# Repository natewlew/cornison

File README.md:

# Cornison

A split mechanical keyboard based on [foostan](https://github.com/foostan)'s
[Corne Cherry v3](https://github.com/foostan/crkbd/tree/v3-final), with a few extra keys
added in a [Keebio Levinson](https://github.com/Keebio/Levinson)-style
layout (an ortholinear grid-plus-thumb-keys arrangement in the same family
as [Let's Split](https://github.com/qmk/qmk_firmware/tree/master/keyboards/lets_split)) —
the name is a mix of **Corne** and **Levinson**.

- **Left half:** the standard Corne 3×6 grid, plus 3 thumb keys and
  dedicated Ctrl, Alt, and Cmd keys.
- **Right half:** the standard Corne 3×6 grid, plus 2 thumb keys and 4
  arrow keys.
- 48 keys total, Kailh/Gateron hotswap sockets (no soldering switches),
  Pro Micro (or Elite-C/Sea-Picro EXT) controller per half, OLED display,
  TRRS between halves, optional per-key and underglow RGB LEDs.
- A 3D-printed case and switch plate, generated directly from the PCB
  rather than hand-modeled, so it stays in sync with any board change.

## Status

**v1.1 is built and in daily use.** Confirmed on real hardware:

- Every key on both halves, the split link over TRRS, and the OLEDs.
- The printed case, FR4 switch plate, inset MCU cover and tenting legs,
  all from the files in this repo.
- A printed PETG switch plate and the spacer frame.
- Pro Micro (Caterina bootloader) as the controller.

Not tested yet:

- Per-key and underglow RGB LEDs.
- Elite-C and Sea-Picro EXT, which should be pin-compatible.
- POM and MJF nylon plates (the FR4 plate and a PETG print have been
  built).

## Gallery

*Last photo: the first build, on a v1.0 board, in an earlier all-black
case with black cover and tenting legs.*

## Repository layout

| Path | What's in it |
|---|---|
| `pcb/` | KiCad project (schematic, PCB, both halves in one panel) |
| `pcb/kbd/` | [foostan/kbd](https://github.com/foostan/kbd) footprint/symbol library (submodule) |
| `build.sh` | Runs every generator — see [Build commands](#build-commands) |
| `case/` | Case, switch plate and MCU cover generator — see [case/README.md](case/README.md) |
| `case/scripts/` | The generator scripts `build.sh` calls |
| `case/out/` | Generated STEP/STL/DXF for the case and plates (gitignored, regenerate locally) |
| `case/plate-fr4-{left,right}/` | KiCad projects for ordering the switch plate in FR4 |
| `firmware/qmk/cornison/` | QMK keyboard definition — see [Firmware](#firmware) below |
| `docs/` | [Build guide](docs/buildguide.md) — parts list and step-by-step assembly |

## Editing the PCB

Open `pcb/cornison.kicad_pro` in KiCad. `pcb/kbd` is a git submodule — after
cloning, run:

```sh
git submodule update --init --recursive
```

## Regenerating the case and plates

The case and plates are generated from the PCB, not drawn by hand. After
any change to the PCB:

```sh
./build.sh case
```

That runs the whole pipeline. Each step is also its own command:

## Build commands

| Command | What it does |
|---|---|
| `./build.sh extract` | Reads the PCB and writes `case/board.json` |
| `./build.sh generate` | Reads `case/board.json` and writes the case, plates, MCU cover, spacers and tents (STEP/STL/DXF) to `case/out/` |
| `./build.sh fr4` | Turns the plate DXF into the KiCad projects in `case/plate-fr4-{left,right}/`. **Overwrites those tracked files**, which are what gets sent to JLCPCB |
| `./build.sh drc` | Runs KiCad's design rule check on both FR4 plate projects |
| `./build.sh case` | All four above, in that order |
| `./build.sh layout` | Regenerates the QMK `LAYOUT` from the PCB into `firmware/qmk/layout.generated.json` |
| `./build.sh help` | Lists the commands |

Requirements: KiCad (for `extract`, `layout` and `drc`) and
[uv](https://docs.astral.sh/uv/) (for `generate` and `fr4`).
`extract` and `layout` need the python3 bundled with KiCad; if it isn't at
the default macOS path, set `KICAD_PYTHON` to it.

See [case/README.md](case/README.md) for the full write-up: stack-up
heights, mounting hardware, assembly order, and how to order each part.

## Firmware

`firmware/qmk/cornison/` is a standalone QMK keyboard definition (not a
QMK fork) - symlink or copy it into a QMK checkout as `keyboards/cornison`
to build it:

```sh
ln -s "$(pwd)/firmware/qmk/cornison" /path/to/qmk_firmware/keyboards/cornison
cd /path/to/qmk_firmware
qmk compile -kb cornison -km default
```

Its `matrix_pins` and matrix topology are copied from upstream QMK's
`crkbd/rev1` (same Pro Micro pinout, same split/OLED setup) - cornison's
own difference is a full 6-column bottom row per half (dedicated
Ctrl/Alt/Cmd + 3 thumb keys on the left, 4 arrow keys + 2 thumb keys on
the right) instead of crkbd's 3-key thumb cluster, so it needs its own
`LAYOUT` rather than reusing crkbd's.

`firmware/qmk/gen_layout.py` (run with `./build.sh layout`) derives that `LAYOUT` array - matrix row/col and
key positions - straight from `pcb/cornison.kicad_pcb`, so it can be
regenerated after any PCB change instead of hand-edited. See
[firmware/qmk/cornison/readme.md](firmware/qmk/cornison/readme.md) for
flashing, bootloader, and handedness setup.

## 3D printing the case

**Download:** the [latest release](https://github.com/natewlew/cornison/releases/latest)
has every STL ready to print (`cornison-v1.1-printed-parts-stl.zip`).

**Or generate them yourself** into `case/out/` (they aren't checked in).
`case/board.json` is in the repo, so this needs only
[uv](https://docs.astral.sh/uv/), not KiCad:

```sh
./build.sh generate
```

Print one of each part per half, unless the table says otherwise:

| Part | Files | Needed? | Orientation |
|---|---|---|---|
| Case | `case-{left,right}.stl` | Yes | Floor down |
| Plate-mount spacers | `spacer-{pom,fr4,mjf}.stl` (4 per half) and `spacer-narrow-{pom,fr4,mjf}.stl` (1 per half) | Yes, unless you skip the plate mount. Pick the set that matches your plate material: the spacer height depends on the plate's thickness | — |
| …or a spacer frame | `spacer-frame-{pom,fr4,mjf}-{left,right}.stl` | Replaces the 10 loose spacers | Top face down, pilots up |
| MCU cover | `cover-inset-{left,right}.stl` | Yes (covers the Pro Micro, TRRS jack and reset switch, with a window for the OLED) | Top face down, posts up |
| Tenting legs | `tent-{left,right}.stl` | Optional, 18° | Flat mounting face down, legs up |
| Switch plate | `plate-pom-{left,right}.stl` (1.5mm) or `plate-mjf-{left,right}.stl` (2.0mm) | Only if you aren't ordering the FR4 plate | Flat |
| Cutting templates | `mat-template-{left,right}.stl`, `foam-plate-template-{left,right}.stl` | Only for the optional floor mat or foam | Flat (0.6mm) |

None of these need supports. Each run of `./build.sh generate` also
writes STEP files for every part (for a service that prefers them) and
deletes the old files in `case/out/` first.

**Home printer (FDM):** PETG works well; PLA is fine for a fit check but
more brittle. Dry PETG before printing: an undried spool leaves
rough, separated top surfaces. The walls are thin, so 4 perimeters
helps. Heat-set inserts go into a PETG case the same way as MJF.

The parts in the photos were printed on a Bambu Lab P1S in Prusament
PETG: Galaxy Black for the cases, Chalky Blue for the tents and covers.
The switch plate in the finished keyboard is FR4, ordered from JLCPCB;
the printed plate and spacer frame above are Prusament PETG. Bambu Lab's own PETG
Matte (black and white) also works and may print a little cleaner on a
Bambu printer, since its profiles are tuned for it. The Prusament colours
just look better.

**Print service:** MJF PA12 nylon (JLC3DP or similar) is the recommended
material, and takes heat-set inserts well. SLA resin works too, but glue
the inserts in instead of heat-setting them. Home and service prints use
the same files.

See [case/README.md](case/README.md) for each part in detail: the
stack-up, mounting hardware, the hardware BOM, and the assembly order.

## Ordering

The [latest release](https://github.com/natewlew/cornison/releases/latest)
has all of these files in one place.

- **PCB:** upload the Gerbers in `pcb/production/` to a fab (JLCPCB).
- **Switch plate (FR4):** upload `case/plate-fr4-{left,right}/production/`
  to a fab as two separate PCB orders — see
  [case/README.md](case/README.md#ordering-the-plate) for settings.
- **Case and other printed parts:** print them at home or send them to a
  3D-print service, see [3D printing the case](#3d-printing-the-case).

## Credits

Based on [foostan/crkbd](https://github.com/foostan/crkbd/tree/v3-final) (MIT licensed).
Uses the [foostan/kbd](https://github.com/foostan/kbd) footprint/symbol
library. See [LICENSE](LICENSE).

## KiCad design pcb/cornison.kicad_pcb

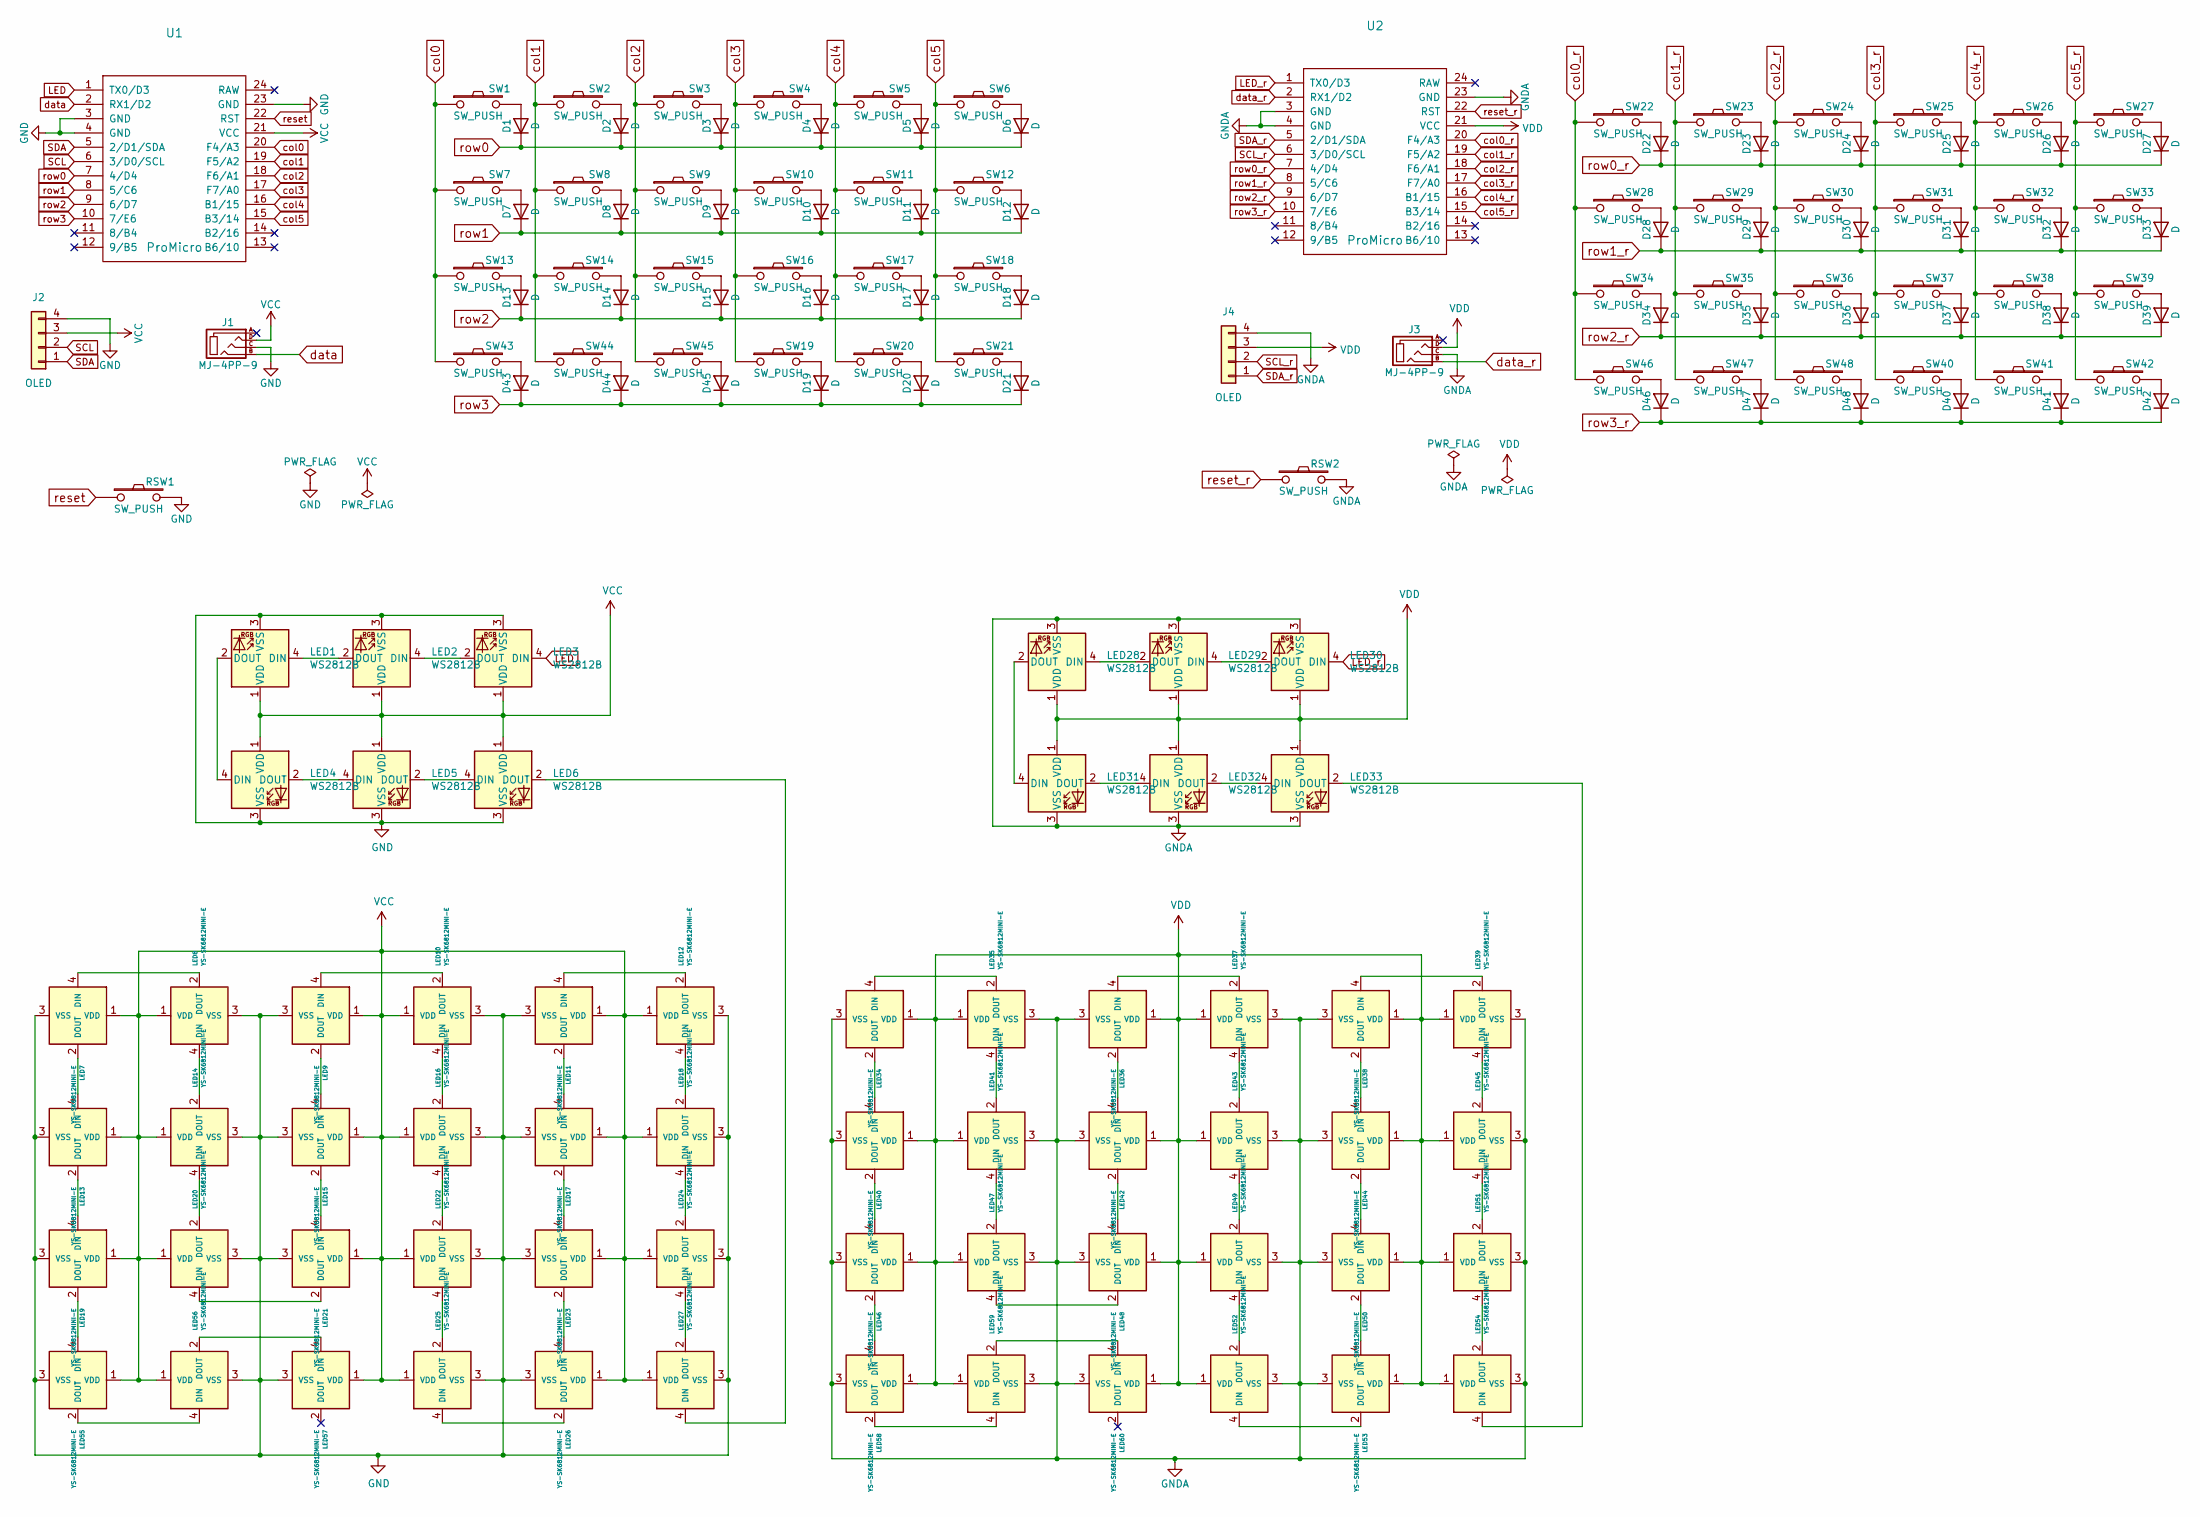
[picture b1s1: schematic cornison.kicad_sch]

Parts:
D1, D2, D3, D4, D5, D6, D7, D8, D9, D10, D11, D12, D13, D14, D15, D16, D17, D18, D19, D20, D21, D22, D23, D24, D25, D26, D27, D28, D29, D30, D31, D32, D33, D34, D35, D36, D37, D38, D39, D40, D41, D42, D43, D44, D45, D46, D47, D48: D; D3_SMD_v2
J1, J3: MJ-4PP-9; MJ-4PP-9_1side
J2, J4: OLED; OLED_1side
LED1, LED2, LED3, LED4, LED5, LED6, LED28, LED29, LED30, LED31, LED32, LED33: WS2812B; LED_WS2812B_PLCC4_5.0x5.0mm_P3.2mm
LED7, LED8, LED9, LED10, LED11, LED12, LED13, LED14, LED15, LED16, LED17, LED18, LED19, LED20, LED21, LED22, LED23, LED24, LED25, LED26, LED27, LED34, LED35, LED36, LED37, LED38, LED39, LED40, LED41, LED42, LED43, LED44, LED45, LED46, LED47, LED48, LED49, LED50, LED51, LED52, LED53, LED54, LED55, LED56, LED57, LED58, LED59, LED60: YS-SK6812MINI-E
RSW1, RSW2: SW_PUSH; ResetSW_1side
SW1, SW2, SW3, SW4, SW5, SW6, SW7, SW8, SW9, SW10, SW11, SW12, SW13, SW14, SW15, SW16, SW17, SW18, SW19, SW20, SW22, SW23, SW24, SW25, SW26, SW27, SW28, SW29, SW30, SW31, SW32, SW33, SW34, SW35, SW36, SW37, SW38, SW39, SW40, SW41, SW43, SW44, SW45, SW46, SW47, SW48: SW_PUSH; CherryMX_Hotswap
SW21, SW42: SW_PUSH; CherryMX_Hotswap_1.5u
U1, U2: ProMicro; ProMicro_v3

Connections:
GND: J1.C, J2.4, LED1.3 (VSS), LED2.3 (VSS), LED3.3 (VSS), LED4.3 (VSS), LED5.3 (VSS), LED6.3 (VSS), LED7.3 (VSS), LED8.3 (VSS), LED9.3 (VSS), LED10.3 (VSS), LED11.3 (VSS), LED12.3 (VSS), LED13.3 (VSS), LED14.3 (VSS), LED15.3 (VSS), LED16.3 (VSS), LED17.3 (VSS), LED18.3 (VSS), LED19.3 (VSS), LED20.3 (VSS), LED21.3 (VSS), LED22.3 (VSS), LED23.3 (VSS), LED24.3 (VSS), LED25.3 (VSS), LED26.3 (VSS), LED27.3 (VSS), LED55.3 (VSS), LED56.3 (VSS), LED57.3 (VSS), RSW1.2, U1.3 (GND), U1.4 (GND), U1.23 (GND)
GNDA: J3.C, J4.4, LED28.3 (VSS), LED29.3 (VSS), LED30.3 (VSS), LED31.3 (VSS), LED32.3 (VSS), LED33.3 (VSS), LED34.3 (VSS), LED35.3 (VSS), LED36.3 (VSS), LED37.3 (VSS), LED38.3 (VSS), LED39.3 (VSS), LED40.3 (VSS), LED41.3 (VSS), LED42.3 (VSS), LED43.3 (VSS), LED44.3 (VSS), LED45.3 (VSS), LED46.3 (VSS), LED47.3 (VSS), LED48.3 (VSS), LED49.3 (VSS), LED50.3 (VSS), LED51.3 (VSS), LED52.3 (VSS), LED53.3 (VSS), LED54.3 (VSS), LED58.3 (VSS), LED59.3 (VSS), LED60.3 (VSS), RSW2.2, U2.3 (GND), U2.4 (GND), U2.23 (GND)
LED: LED3.4 (DIN), U1.1 (TX0/D3)
LED_r: LED30.4 (DIN), U2.1 (TX0/D3)
unnamed: D1.2 (A), SW1.2
unnamed: D2.2 (A), SW2.2
unnamed: D3.2 (A), SW3.2
unnamed: D4.2 (A), SW4.2
unnamed: D5.2 (A), SW5.2
unnamed: D6.2 (A), SW6.2
unnamed: D7.2 (A), SW7.2
unnamed: D8.2 (A), SW8.2
unnamed: D9.2 (A), SW9.2
unnamed: D10.2 (A), SW10.2
unnamed: D11.2 (A), SW11.2
unnamed: D12.2 (A), SW12.2
unnamed: D13.2 (A), SW13.2
unnamed: D14.2 (A), SW14.2
unnamed: D15.2 (A), SW15.2
unnamed: D16.2 (A), SW16.2
unnamed: D17.2 (A), SW17.2
unnamed: D18.2 (A), SW18.2
unnamed: D19.2 (A), SW19.2
unnamed: D20.2 (A), SW20.2
unnamed: D21.2 (A), SW21.2
unnamed: D22.2 (A), SW22.2
unnamed: D23.2 (A), SW23.2
unnamed: D24.2 (A), SW24.2
unnamed: D25.2 (A), SW25.2
unnamed: D26.2 (A), SW26.2
unnamed: D27.2 (A), SW27.2
unnamed: D28.2 (A), SW28.2
unnamed: D29.2 (A), SW29.2
unnamed: D30.2 (A), SW30.2
unnamed: D31.2 (A), SW31.2
unnamed: D32.2 (A), SW32.2
unnamed: D33.2 (A), SW33.2
unnamed: D34.2 (A), SW34.2
unnamed: D35.2 (A), SW35.2
unnamed: D36.2 (A), SW36.2
unnamed: D37.2 (A), SW37.2
unnamed: D38.2 (A), SW38.2
unnamed: D39.2 (A), SW39.2
unnamed: D40.2 (A), SW40.2
unnamed: D41.2 (A), SW41.2
unnamed: D42.2 (A), SW42.2
unnamed: D43.2 (A), SW43.2
unnamed: D44.2 (A), SW44.2
unnamed: D45.2 (A), SW45.2
unnamed: D46.2 (A), SW46.2
unnamed: D47.2 (A), SW47.2
unnamed: D48.2 (A), SW48.2
unnamed: LED1.4 (DIN), LED2.2 (DOUT)
unnamed: LED1.2 (DOUT), LED4.4 (DIN)
unnamed: LED2.4 (DIN), LED3.2 (DOUT)
unnamed: LED4.2 (DOUT), LED5.4 (DIN)
unnamed: LED5.2 (DOUT), LED6.4 (DIN)
unnamed: LED7.4 (DIN), LED8.2 (DOUT)
unnamed: LED10.4 (DIN), LED16.2 (DOUT)
unnamed: LED9.4 (DIN), LED10.2 (DOUT)
unnamed: LED11.4 (DIN), LED12.2 (DOUT)
unnamed: LED11.2 (DOUT), LED17.4 (DIN)
unnamed: LED12.4 (DIN), LED18.2 (DOUT)
unnamed: LED7.2 (DOUT), LED13.4 (DIN)
unnamed: LED13.2 (DOUT), LED19.4 (DIN)
unnamed: LED14.4 (DIN), LED20.2 (DOUT)
unnamed: LED8.4 (DIN), LED14.2 (DOUT)
unnamed: LED9.2 (DOUT), LED15.4 (DIN)
unnamed: LED15.2 (DOUT), LED21.4 (DIN)
unnamed: LED16.4 (DIN), LED22.2 (DOUT)
unnamed: LED17.2 (DOUT), LED23.4 (DIN)
unnamed: LED18.4 (DIN), LED24.2 (DOUT)
unnamed: LED19.2 (DOUT), LED55.4 (DIN)
unnamed: LED20.4 (DIN), LED21.2 (DOUT)
unnamed: LED22.4 (DIN), LED25.2 (DOUT)
unnamed: LED23.2 (DOUT), LED26.4 (DIN)
unnamed: LED24.4 (DIN), LED27.2 (DOUT)
unnamed: LED25.4 (DIN), LED26.2 (DOUT)
unnamed: LED6.2 (DOUT), LED27.4 (DIN)
unnamed: LED28.4 (DIN), LED29.2 (DOUT)
unnamed: LED28.2 (DOUT), LED31.4 (DIN)
unnamed: LED29.4 (DIN), LED30.2 (DOUT)
unnamed: LED31.2 (DOUT), LED32.4 (DIN)
unnamed: LED32.2 (DOUT), LED33.4 (DIN)
unnamed: LED33.2 (DOUT), LED54.4 (DIN)
unnamed: LED34.4 (DIN), LED35.2 (DOUT)
unnamed: LED34.2 (DOUT), LED40.4 (DIN)
unnamed: LED35.4 (DIN), LED41.2 (DOUT)
unnamed: LED36.4 (DIN), LED37.2 (DOUT)
unnamed: LED36.2 (DOUT), LED42.4 (DIN)
unnamed: LED37.4 (DIN), LED43.2 (DOUT)
unnamed: LED38.4 (DIN), LED39.2 (DOUT)
unnamed: LED38.2 (DOUT), LED44.4 (DIN)
unnamed: LED39.4 (DIN), LED45.2 (DOUT)
unnamed: LED40.2 (DOUT), LED46.4 (DIN)
unnamed: LED41.4 (DIN), LED47.2 (DOUT)
unnamed: LED42.2 (DOUT), LED48.4 (DIN)
unnamed: LED43.4 (DIN), LED49.2 (DOUT)
unnamed: LED44.2 (DOUT), LED50.4 (DIN)
unnamed: LED45.4 (DIN), LED51.2 (DOUT)
unnamed: LED46.2 (DOUT), LED58.4 (DIN)
unnamed: LED47.4 (DIN), LED48.2 (DOUT)
unnamed: LED49.4 (DIN), LED52.2 (DOUT)
unnamed: LED50.2 (DOUT), LED53.4 (DIN)
unnamed: LED51.4 (DIN), LED54.2 (DOUT)
unnamed: LED52.4 (DIN), LED53.2 (DOUT)
unnamed: LED55.2 (DOUT), LED56.4 (DIN)
unnamed: LED56.2 (DOUT), LED57.4 (DIN)
unnamed: LED58.2 (DOUT), LED59.4 (DIN)
unnamed: LED59.2 (DOUT), LED60.4 (DIN)
SCL: J2.2, U1.6 (3/D0/SCL)
SCL_r: J4.2, U2.6 (3/D0/SCL)
SDA: J2.1, U1.5 (2/D1/SDA)
SDA_r: J4.1, U2.5 (2/D1/SDA)
VCC: J1.D, J2.3, LED1.1 (VDD), LED2.1 (VDD), LED3.1 (VDD), LED4.1 (VDD), LED5.1 (VDD), LED6.1 (VDD), LED7.1 (VDD), LED8.1 (VDD), LED9.1 (VDD), LED10.1 (VDD), LED11.1 (VDD), LED12.1 (VDD), LED13.1 (VDD), LED14.1 (VDD), LED15.1 (VDD), LED16.1 (VDD), LED17.1 (VDD), LED18.1 (VDD), LED19.1 (VDD), LED20.1 (VDD), LED21.1 (VDD), LED22.1 (VDD), LED23.1 (VDD), LED24.1 (VDD), LED25.1 (VDD), LED26.1 (VDD), LED27.1 (VDD), LED55.1 (VDD), LED56.1 (VDD), LED57.1 (VDD), U1.21 (VCC)
VDD: J3.D, J4.3, LED28.1 (VDD), LED29.1 (VDD), LED30.1 (VDD), LED31.1 (VDD), LED32.1 (VDD), LED33.1 (VDD), LED34.1 (VDD), LED35.1 (VDD), LED36.1 (VDD), LED37.1 (VDD), LED38.1 (VDD), LED39.1 (VDD), LED40.1 (VDD), LED41.1 (VDD), LED42.1 (VDD), LED43.1 (VDD), LED44.1 (VDD), LED45.1 (VDD), LED46.1 (VDD), LED47.1 (VDD), LED48.1 (VDD), LED49.1 (VDD), LED50.1 (VDD), LED51.1 (VDD), LED52.1 (VDD), LED53.1 (VDD), LED54.1 (VDD), LED58.1 (VDD), LED59.1 (VDD), LED60.1 (VDD), U2.21 (VCC)
col0: SW1.1, SW7.1, SW13.1, SW43.1, U1.20 (F4/A3)
col0_r: SW22.1, SW28.1, SW34.1, SW46.1, U2.20 (F4/A3)
col1: SW2.1, SW8.1, SW14.1, SW44.1, U1.19 (F5/A2)
col1_r: SW23.1, SW29.1, SW35.1, SW47.1, U2.19 (F5/A2)
col2: SW3.1, SW9.1, SW15.1, SW45.1, U1.18 (F6/A1)
col2_r: SW24.1, SW30.1, SW36.1, SW48.1, U2.18 (F6/A1)
col3: SW4.1, SW10.1, SW16.1, SW19.1, U1.17 (F7/A0)
col3_r: SW25.1, SW31.1, SW37.1, SW40.1, U2.17 (F7/A0)
col4: SW5.1, SW11.1, SW17.1, SW20.1, U1.16 (B1/15)
col4_r: SW26.1, SW32.1, SW38.1, SW41.1, U2.16 (B1/15)
col5: SW6.1, SW12.1, SW18.1, SW21.1, U1.15 (B3/14)
col5_r: SW27.1, SW33.1, SW39.1, SW42.1, U2.15 (B3/14)
data: J1.B, U1.2 (RX1/D2)
data_r: J3.B, U2.2 (RX1/D2)
reset: RSW1.1, U1.22 (RST)
reset_r: RSW2.1, U2.22 (RST)
row0: D1.1 (K), D2.1 (K), D3.1 (K), D4.1 (K), D5.1 (K), D6.1 (K), U1.7 (4/D4)
row0_r: D22.1 (K), D23.1 (K), D24.1 (K), D25.1 (K), D26.1 (K), D27.1 (K), U2.7 (4/D4)
row1: D7.1 (K), D8.1 (K), D9.1 (K), D10.1 (K), D11.1 (K), D12.1 (K), U1.8 (5/C6)
row1_r: D28.1 (K), D29.1 (K), D30.1 (K), D31.1 (K), D32.1 (K), D33.1 (K), U2.8 (5/C6)
row2: D13.1 (K), D14.1 (K), D15.1 (K), D16.1 (K), D17.1 (K), D18.1 (K), U1.9 (6/D7)
row2_r: D34.1 (K), D35.1 (K), D36.1 (K), D37.1 (K), D38.1 (K), D39.1 (K), U2.9 (6/D7)
row3: D19.1 (K), D20.1 (K), D21.1 (K), D43.1 (K), D44.1 (K), D45.1 (K), U1.10 (7/E6)
row3_r: D40.1 (K), D41.1 (K), D42.1 (K), D46.1 (K), D47.1 (K), D48.1 (K), U2.10 (7/E6)

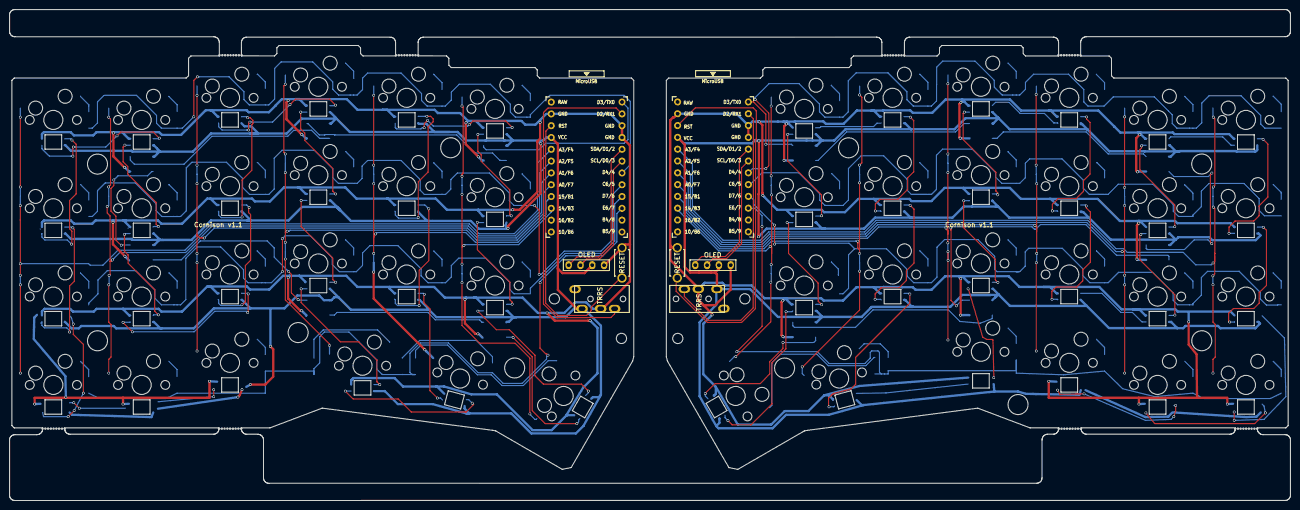
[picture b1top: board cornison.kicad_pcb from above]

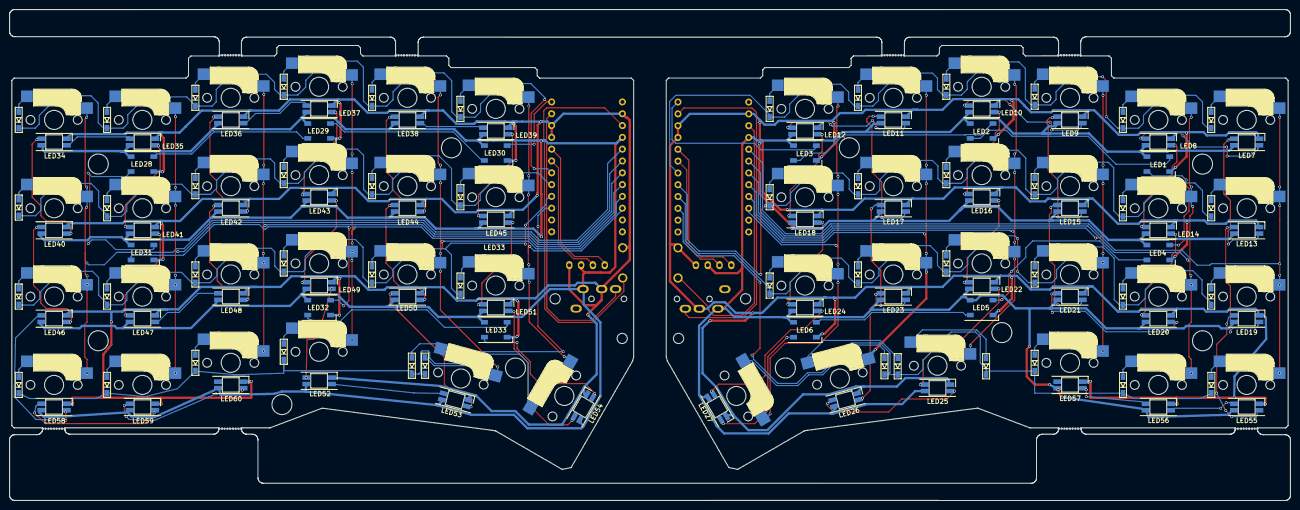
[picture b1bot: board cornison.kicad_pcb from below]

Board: 2 copper layers, 275.5 x 105.6 mm, 178 parts (111 on the bottom side), 140 nets.

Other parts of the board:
Ref**: Val**; M2_HOLE_v2
Ref**#2, Ref**#3, Ref**#4, Ref**#5, Ref**#6, Ref**#7, Ref**#8, Ref**#9, Ref**#10, Ref**#11, Ref**#12, Ref**#13, Ref**#14: Val**; M2_HOLE_v2

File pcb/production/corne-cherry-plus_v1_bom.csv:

Designator,Footprint,Quantity,Value,LCSC Part #
"D1, D10, D11, D12, D13, D14, D15, D16, D17, D18, D19, D2, D20, D21, D22, D23, D24, D25, D26, D27, D28, D29, D3, D30, D31, D32, D33, D34, D35, D36, D37, D38, D39, D4, D40, D41, D42, D43, D44, D45, D46, D47, D48, D5, D6, D7, D8, D9",D3_SMD_v2,48,D,
"J1, J3",MJ-4PP-9_1side,2,MJ-4PP-9,
"J2, J4",OLED_1side,2,OLED,
"LED1, LED2, LED28, LED29, LED3, LED30, LED31, LED32, LED33, LED4, LED5, LED6",LED_WS2812B_PLCC4_5.0x5.0mm_P3.2mm,12,WS2812B,
"LED10, LED11, LED12, LED13, LED14, LED15, LED16, LED17, LED18, LED19, LED20, LED21, LED22, LED23, LED24, LED25, LED26, LED27, LED34, LED35, LED36, LED37, LED38, LED39, LED40, LED41, LED42, LED43, LED44, LED45, LED46, LED47, LED48, LED49, LED50, LED51, LED52, LED53, LED54, LED7, LED8, LED9",YS-SK6812MINI-E,42,YS-SK6812MINI-E,
"RSW1, RSW2",ResetSW_1side,2,SW_PUSH,
"SW1, SW10, SW11, SW12, SW13, SW14, SW15, SW16, SW17, SW18, SW19, SW2, SW20, SW22, SW23, SW24, SW25, SW26, SW27, SW28, SW29, SW3, SW30, SW31, SW32, SW33, SW34, SW35, SW36, SW37, SW38, SW39, SW4, SW40, SW41, SW43, SW44, SW45, SW46, SW47, SW48, SW5, SW6, SW7, SW8, SW9",CherryMX_Hotswap,46,SW_PUSH,
"SW21, SW42",CherryMX_Hotswap_1.5u,2,SW_PUSH,
"U1, U2",ProMicro_v3,2,ProMicro,
